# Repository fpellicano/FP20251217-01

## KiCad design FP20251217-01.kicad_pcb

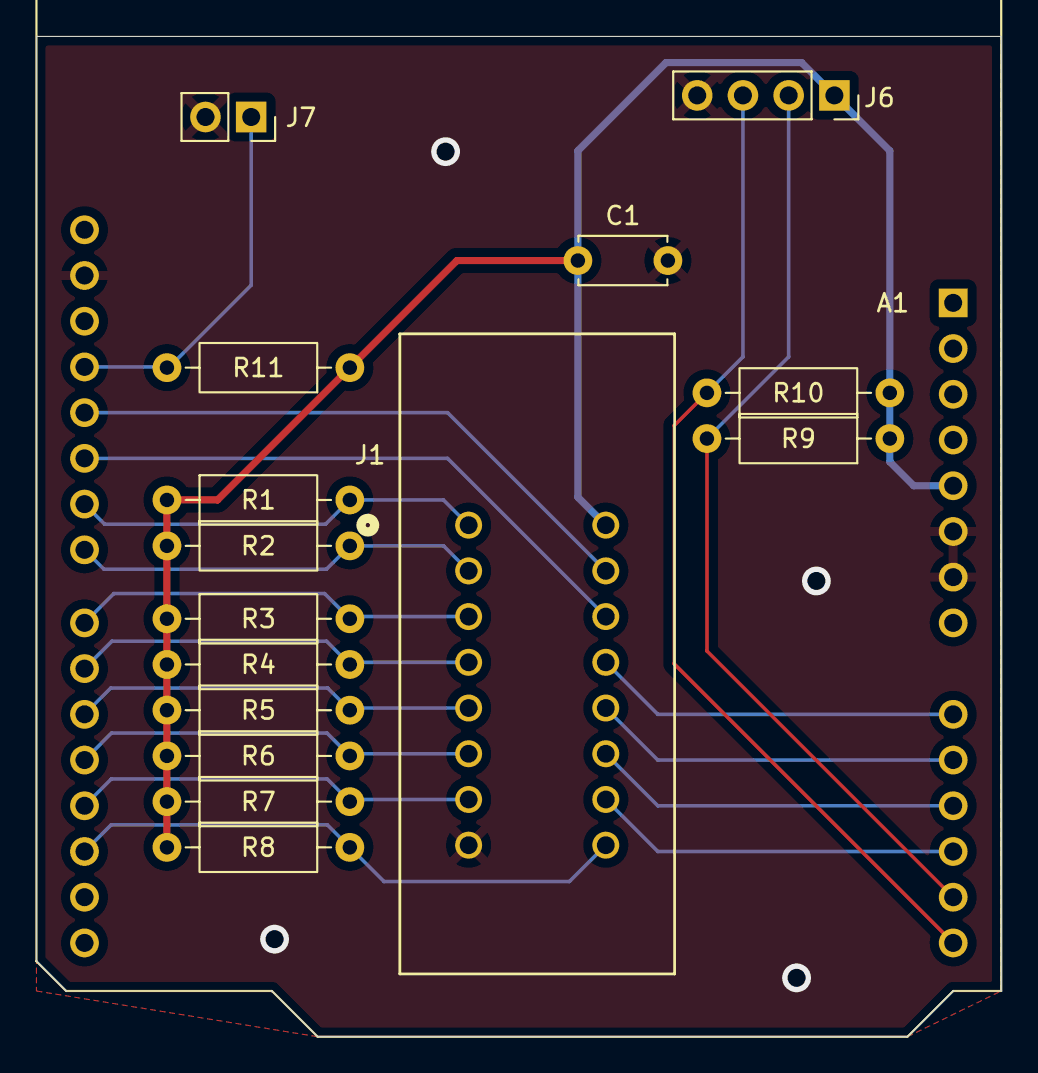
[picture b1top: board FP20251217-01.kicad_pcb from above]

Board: 2 copper layers, 53.6 x 55.6 mm, 16 parts (0 on the bottom side), 19 nets.

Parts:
A1: Arduino_UNO_R2
C1: 0.1u; C_Disc_D4.7mm_W2.5mm_P5.00mm
J1: 216-3340-00-0602J; CONN_216-3340-00-0602J_3MM
J6: Display; PinSocket_1x04_P2.54mm_Vertical
J7: Read Button; PinSocket_1x02_P2.54mm_Vertical
R1, R2, R3, R4, R5, R6, R7, R8, R9, R10, R11: 10k; R_Axial_DIN0207_L6.3mm_D2.5mm_P10.16mm_Horizontal

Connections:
+5V: A1.5 (+5V), C1.1, J1.16 (VCC), J6.1, R1.1, R2.1, R3.1, R4.1, R5.1, R6.1, R7.1, R8.1, R9.1, R10.1, R11.1
/A0: A1.12 (A3), J1.10 (A0)
/A1: A1.11 (A2), J1.11 (A1)
/A2: A1.10 (A1), J1.12 (A2)
/A3: A1.9 (A0), J1.13 (A3)
/A4: A1.25 (D10), J1.14 (A4)
/O1: A1.24 (D9), J1.1 (O1), R1.2
/O2: A1.23 (D8), J1.2 (O2), R2.2
/O3: A1.22 (D7), J1.3 (O3), R3.2
/O4: A1.21 (D6), J1.4 (O4), R4.2
/O5: A1.20 (D5), J1.5 (O5), R5.2
/O6: A1.19 (D4), J1.6 (O6), R6.2
/O7: A1.18 (D3), J1.7 (O7), R7.2
/O8: A1.17 (D2), J1.9 (O8), R8.2
/PB: A1.27 (D12), J7.1, R11.2
/SCL: A1.14 (SCL/A5), J6.3, R10.2
/SDA: A1.13 (SDA/A4), J6.2, R9.2
/~CE: A1.26 (D11), J1.15 (~CE)
GND: A1.6 (GND), A1.7 (GND), A1.29 (GND), C1.2, J1.8 (GND), J6.4, J7.2

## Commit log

2025-12-18 Roughing out PCB
2025-12-18 Added planes
    Since holes will not inherently be plated through holes, I tried to maintain connection to components entirely on one side. A few traces are on the top side, with the intention of them be soldered fr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
2025-12-18 Includes arduino module on sch
